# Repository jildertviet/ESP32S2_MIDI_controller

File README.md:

# ESP32S2_MIDI_controller
ESP32S2 based MIDI controller with 5 sliders  
It uses the internal DAC of the ESP32 which is quite unstable for this purpose.   
#### !!! So I recommend to redesign the board with an external DAC, a MCP3008 for example.  
(I've stabilized the output with a Kalman filter.)  

# Known issues
- Missing a ground plane
- Noisy values from ADC 
- Footprint of sliders isn't perfect

# Dependancies
- ESP32-S2-WROVER symbol & footprint from snapEDA  
- SimpleKalmanFilter Arduino lib  
- [midiusb.h](https://github.com/chegewara/EspTinyUSB)  
- Maybe some more symbols (ME6211?)  

# Hardware 
[Sliders used (Tinytronics.nl)](https://www.tinytronics.nl/shop/nl/componenten/weerstanden/10k%CF%89-slide-potmeter-standaard-75mm) (had to bend the pins a little bit)

</img>
</img>

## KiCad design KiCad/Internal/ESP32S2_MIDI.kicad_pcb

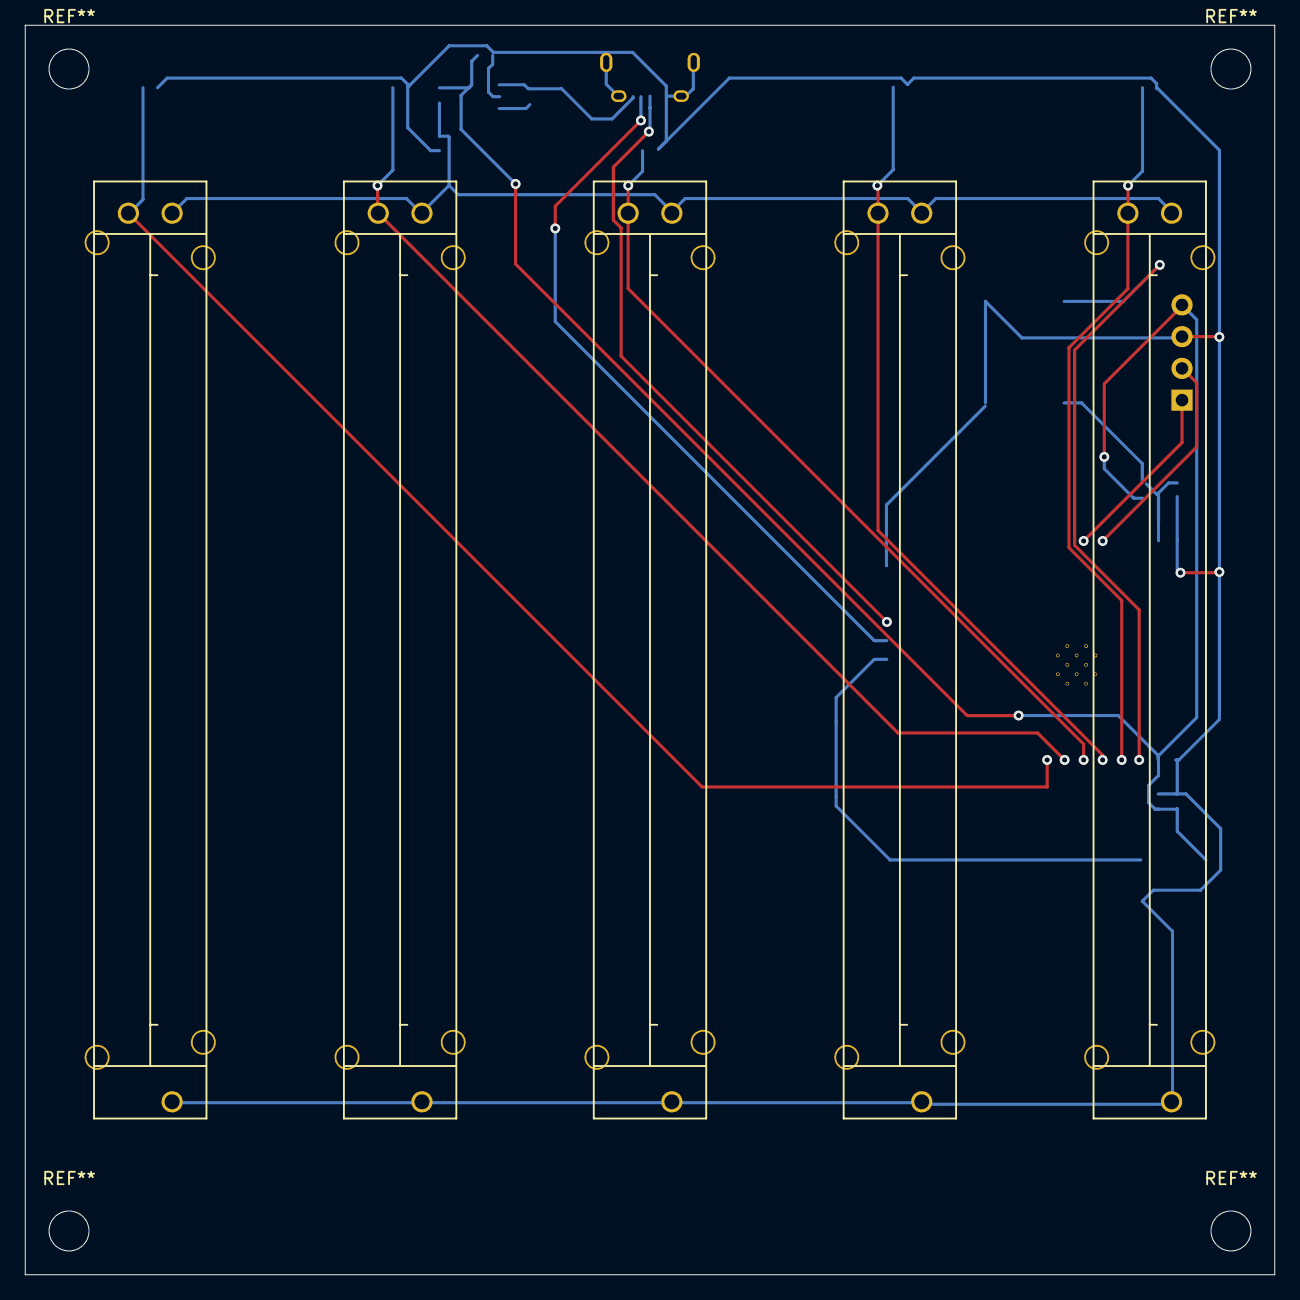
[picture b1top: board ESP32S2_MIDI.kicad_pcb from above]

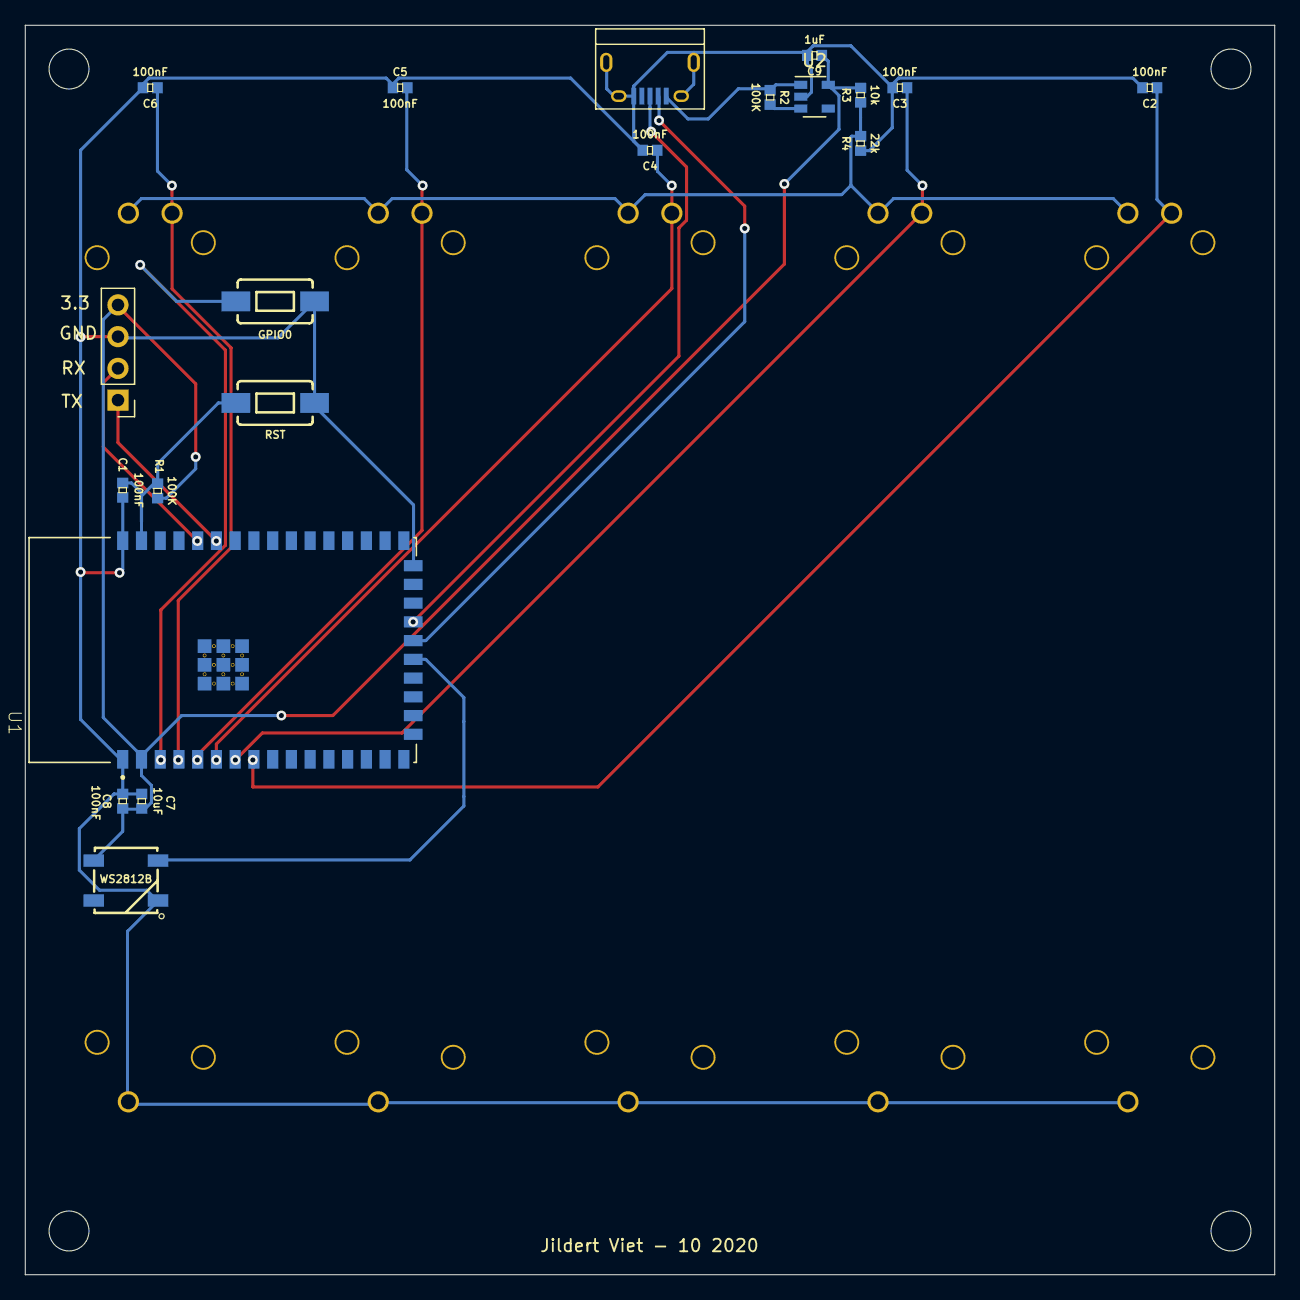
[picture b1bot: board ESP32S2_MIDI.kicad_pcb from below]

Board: 2 copper layers, 100.0 x 100.0 mm, 25 parts (20 on the bottom side), 18 nets.

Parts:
C1, C2, C3, C4, C5, C6, C8: 100nF; 0402
C7: 10uF; 0402
C9: 1uF; 0402
D1: WS2812B
J1: USB_OTG; USB_Micro-B
J2: Conn_01x04_Female; Pin_Header_Straight_1x04_Pitch2.54mm
R1, R2: 100K; 0402
R3: 10k; 0402
R4: 22k; 0402
RV1: Brightness; jildertSlider75
RV2: Alpha; jildertSlider75
RV3: Mask; jildertSlider75
RV4: Cam LR; jildertSlider75
RV5: Cam UD; jildertSlider75
SW1: RST; TACTILE_SWITCH_SMD_6.0X3.5MM
SW2: GPIO0; TACTILE_SWITCH_SMD_6.0X3.5MM
U1: ESP32-S2-WROVER; MODULE_ESP32-S2-WROVER
U2: ME6211; SOT-23-5

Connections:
+1V5: R3.1, R4.2, RV1.1, RV2.1, RV3.1, RV4.1, RV5.1
+3V3: C7.1, C8.1, C9.1, D1.1, J2.4, R1.1, R3.2, U1.2, U2.5
+5V: J1.1, R2.1, U2.1
GND: C1.1, C2.2, C3.2, C4.2, C5.1, C6.2, C7.2, C8.2, C9.2, D1.3, J1.5, J1.6, J2.3, R4.1, RV1.3, RV2.3, RV3.3, RV4.3, RV5.3, SW1.2, SW2.1, U1.1, U1.26, U1.42, U2.2
unnamed: C1.2, R1.2, SW1.1, U1.41
unnamed: C2.1, RV5.2, U1.8
unnamed: C3.1, RV4.2, U1.7
unnamed: C4.1, RV3.2, U1.6
unnamed: C5.2, RV2.2, U1.5
unnamed: C6.1, RV1.2, U1.4
unnamed: D1.4, U1.21
unnamed: R2.2, U2.3
unnamed: SW2.2, U1.3
unnamed: U1.43_1, U1.43_2, U1.43_3, U1.43_4, U1.43_5, U1.43_6, U1.43_7, U1.43_8, U1.43_9, U1.43_10, U1.43_11, U1.43_12, U1.43_13, U1.43_14, U1.43_15, U1.43_16, U1.43_17, U1.43_18, U1.43_19, U1.43_20, U1.43_21
RX: J2.2, U1.38
TX: J2.1, U1.37
USB_D+: J1.3, U1.23
USB_D-: J1.2, U1.22

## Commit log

2020-11-28 Added Arduino sketch
2020-11-28 Removed comments and multipsampling feature
2020-11-28 Added images
2020-11-28 Moving folders
2020-11-28 Adding top plate
